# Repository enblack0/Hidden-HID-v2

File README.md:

# Hidden-HID-v2
Hidden HID v2 is a tiny USB rubber ducky that can be concealed entirely inside the USB port. I have implemented various hardware improvements compared to v1.

These include: 
1. Removal of SWD programming pins to rely only on STs internal USB bootloader, which avoids the need to painstakingly solder the PCB to the STLink debugger every time I want to change the program. Now it is only necessary to bridge the BOOT0 test pad (middle) with 3V3 to select bootloader, or with GND to select application (see image below). After connecting BOOT0 to 3V3, the STM32 can then be programmed by inserting into the USB port and using the STCubeProgrammer tool to download the hex file. 
2. Layout changes to enable easier assembly of the spacer elements
3. Switching the spacer elements from LEDs with no electrical function to IR phototransistors which also provide a simple on-off remote control. This allows the device to be remotely armed and disarmed once inserted.

connect BOOT0 to GND to run application or with 3V3 to reprogram

KiCad files can be found under /KiCad, gerber and BOM separately under /Fabrication.
Under /STM32 I have uploaded a basic test firmware. This firmware waits for an IR signal, then opens a terminal and echoes hello world. You may need to tweak the paths a little to get it running on your system. 

If you are interested in purchasing this PCB, I have uploaded it to the PCBWay community. Here you can order either the bare PCB or the assembled PCB directly: https://www.pcbway.com/project/shareproject/Hidden_HID_an_invisible_USB_Rubber_Ducky_3a8cd27f.html

Also check out the project write-up on hackaday: https://hackaday.io/project/202218-hidden-hid-v2-worlds-smallest-rubber-ducky

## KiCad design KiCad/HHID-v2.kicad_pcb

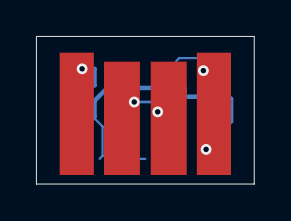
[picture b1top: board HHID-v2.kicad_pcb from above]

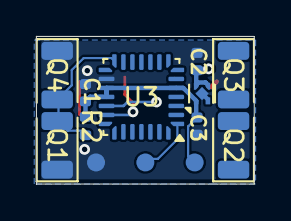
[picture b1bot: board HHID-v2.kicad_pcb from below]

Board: 2 copper layers, 12.1 x 8.2 mm, 14 parts (13 on the bottom side), 7 nets.

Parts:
C1: 4.7µ; C_0402_1005Metric_noSS
C2, C3: 1µ; C_0402_1005Metric_noSS
J1: USB_A; usb-PCB
Q1, Q2, Q3, Q4: Würth 1541201NC3060; LED_1206_3216Metric_IPC_C
R2: 2k2; R_0402_1005Metric_noSS
TP1, TP2, TP3: TestPoint_Pad_D0.8mm
U2: NCP115AMX330TCG; OnSemi_XDFN4-1EP_1.0x1.0mm_EP0.52x0.52mm
U3: STM32F042G6Ux; QFN-28_4x4mm_P0.5mm

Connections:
+3.3V: C1.2, C3.2, R2.1, TP2.1, U2.1 (OUT), U3.5 (VDDA), U3.17 (VDD), U3.18 (VDDIO2)
+5V: C2.1, J1.1 (VBUS), U2.3 (EN), U2.4 (IN)
/BOOT0: TP1.1, U3.1 (PB8)
/DM: J1.2 (D-), U3.19 (PA9/PA11)
/DP: J1.3 (D+), U3.20 (PA10/PA12)
/IR_DET: Q1.1 (C), Q4.1 (C), R2.2, U3.14 (PB0)
GND: C1.1, C2.2, C3.1, J1.4 (GND), Q1.2 (E), Q4.2 (E), TP3.1, U2.2 (GND), U2.5 (GND), U3.16 (VSSA)

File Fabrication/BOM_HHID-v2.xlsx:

Item | Designator | Quantity | Manufacturer | Mfg Part # | Description / Value | Package / Footprint | Type | Mouser Part # | Digikey Part # | Notes
1.0 | C1 | 1.0 |  |  | CAP CER 4.7µF 10V X5R/X7R | 0402 | SMD
2.0 | C2, C3 | 2.0 |  |  | CAP CER 1µF 16V X5R/X7R | 0402 | SMD
3.0 | R2 | 1.0 |  |  | RES 10k 1% | 0402 | SMD
4.0 | Q1, Q2, Q3, Q4 | 4.0 | Würth Elektronik | 1541201NC3060 | Phototransistor IR 940nm | 1206 | SMD | 710-1541201NC3060
5.0 | U3 | 1.0 | STMicroelectronics | STM32F042G6U6 | ARM Microcontrollers - MCU Mainstream Arm Cortex-M0+ MCU 32 Kbytes Flash | UFQFPN-28 | SMD | 511-STM32F042G6U6
6.0 | U2 | 1.0 | onsemi | NCP115AMX330TCG | LDO 3.3V 300mA | XDFN-4 | SMD | 863-NCP115AMX330TCG
